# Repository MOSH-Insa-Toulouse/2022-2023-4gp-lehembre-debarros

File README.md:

# 2022-2023-4gp-lehembre-debarros

## SOMMAIRE 

1. Etapes de fabrication
2. Présentation du capteur graphite 
3. Simulations sous LtSpice
4. Circuit électronique
5. Eléments nécessaires au projet
6. Elaboration du shield sous KiCAD
7. Programme Arduino
8. Application Android
9. Banc de test
10. Datasheet 

# 1. Etapes de fabrication

- Création du circuit et simulations sous LtSpice
- Implémentation du circuit sous KiCAD et élaboration du PCB 
- Fabrication du PCB
- Percage de la plaquette et soudure des composants 
- Elaboration du code Arduino
- Création de l'application d'interfacage sous MIT - app inventor
- Caractérisation du capteur

# 2. Présentation du capteur graphite 

Le capteur est basé sur l'effet tunnel quantique entre les particules de graphite déposées par le crayon. 
Pour plus d'informations, vous pouvez vous renseigner grâce au lien suivant : [Informations supplémentaires](https://github.com/MOSH-Insa-Toulouse/2022-2023-4gp-lehembre-debarros/blob/d776b440ef20fb4f5e64abb67d3f56df1f3a449e/++Publi%20Pencil%20Drawn%20Strain%20Gauges-srep03812.pdf)

Dimensions : 

Utilisation d'un crayon HB pour le grain.

# 3. Simulations sous LtSpice

Etude et dimensionnement du gain et des capacités afin d’obtenir un signal exploitable en simulant le circuit : 

La résistance du capteur est calculé grâce à la formule suivante : 𝑅_𝐶=((𝑅_3+𝑅_2) 𝑅_1 𝑉_𝐶𝐶)/(𝑅_2 𝑉_𝐴𝐷𝐶)−𝑅_5−𝑅_1

# 4. Circuit électronique 

Schéma de l'amplificateur de signal :

Modules supplémentaires et leur connexions : 

Connection des pins entre le PCB et la carte Arduino

# 5. Eléments nécessaires au projet 

-	Arduino Uno
-	Module Bluetooth HC05
-	Amplificateur LTC1050 
-	I2C Ecran OLED Joy-it SBC-OLED01
-	Encodeur rotatoire avec boutton poussoir (Joy-it KY-040) 
-	Spectrasymbol 005 21 Flex Sensor
-	MCP41050 SPI Potentiomètre Digital 

# 6. Elaboration du PCB sous KiCAD

Représentation du PCB avec le circuit implémenté : 

Empruntes des autres composants : 

# 7. Programme Arduino

Ci-après, le code Arduino utilisé : [Code Arduino](https://github.com/MOSH-Insa-Toulouse/2022-2023-4gp-lehembre-debarros/blob/07b504035136efd2108f1f7b01446d1b1bee7c57/Code_arduino_Lauriane_Alan.ino)

# 8. Application Android

L'APK est disponible à cette adresse : [APK](https://github.com/MOSH-Insa-Toulouse/2022-2023-4gp-lehembre-debarros/blob/c0ea48ad6c8dff68e6e4c520c7baa0256ce2a0f2/Capteur_Graphite_Final.apk)

# 9. Banc de test

Pour calibrer notre capteur, nous avons utilisé le banc de test mis à notre disposition. 

Nous avons ainsi obtenu les variations relatives suivantes en tension et en compression : 

Notre capteur dispose ainsi d'une sensibilité de 0,675 GΩ/% en compression et 0,2GΩ/% en tension.

Cette sensibilité correspond au coefficient de la pente de la variation relative par rapport à la déformation. 
La déformation se calcule à l'aide de la formule suivante : ɛ = e/(2.R).

- ɛ : déformation
- e : épaisseur du papier utilisé (0,16mm ici)
- R : rayon de la courbe

These values are for comparative use only to get orders of magnitude, they are very unstable until the sensor is stabilized in a specialized housing. 

# 10. Datasheet

La datasheet est disponible en suivante le lien ci-après : [Datasheet](https://github.com/MOSH-Insa-Toulouse/2022-2023-4gp-lehembre-debarros/blob/0e1e4ce1e155748c3f02e4ec9dddf21011c97965/Datasheet%20-%20Capteur-final.pdf)

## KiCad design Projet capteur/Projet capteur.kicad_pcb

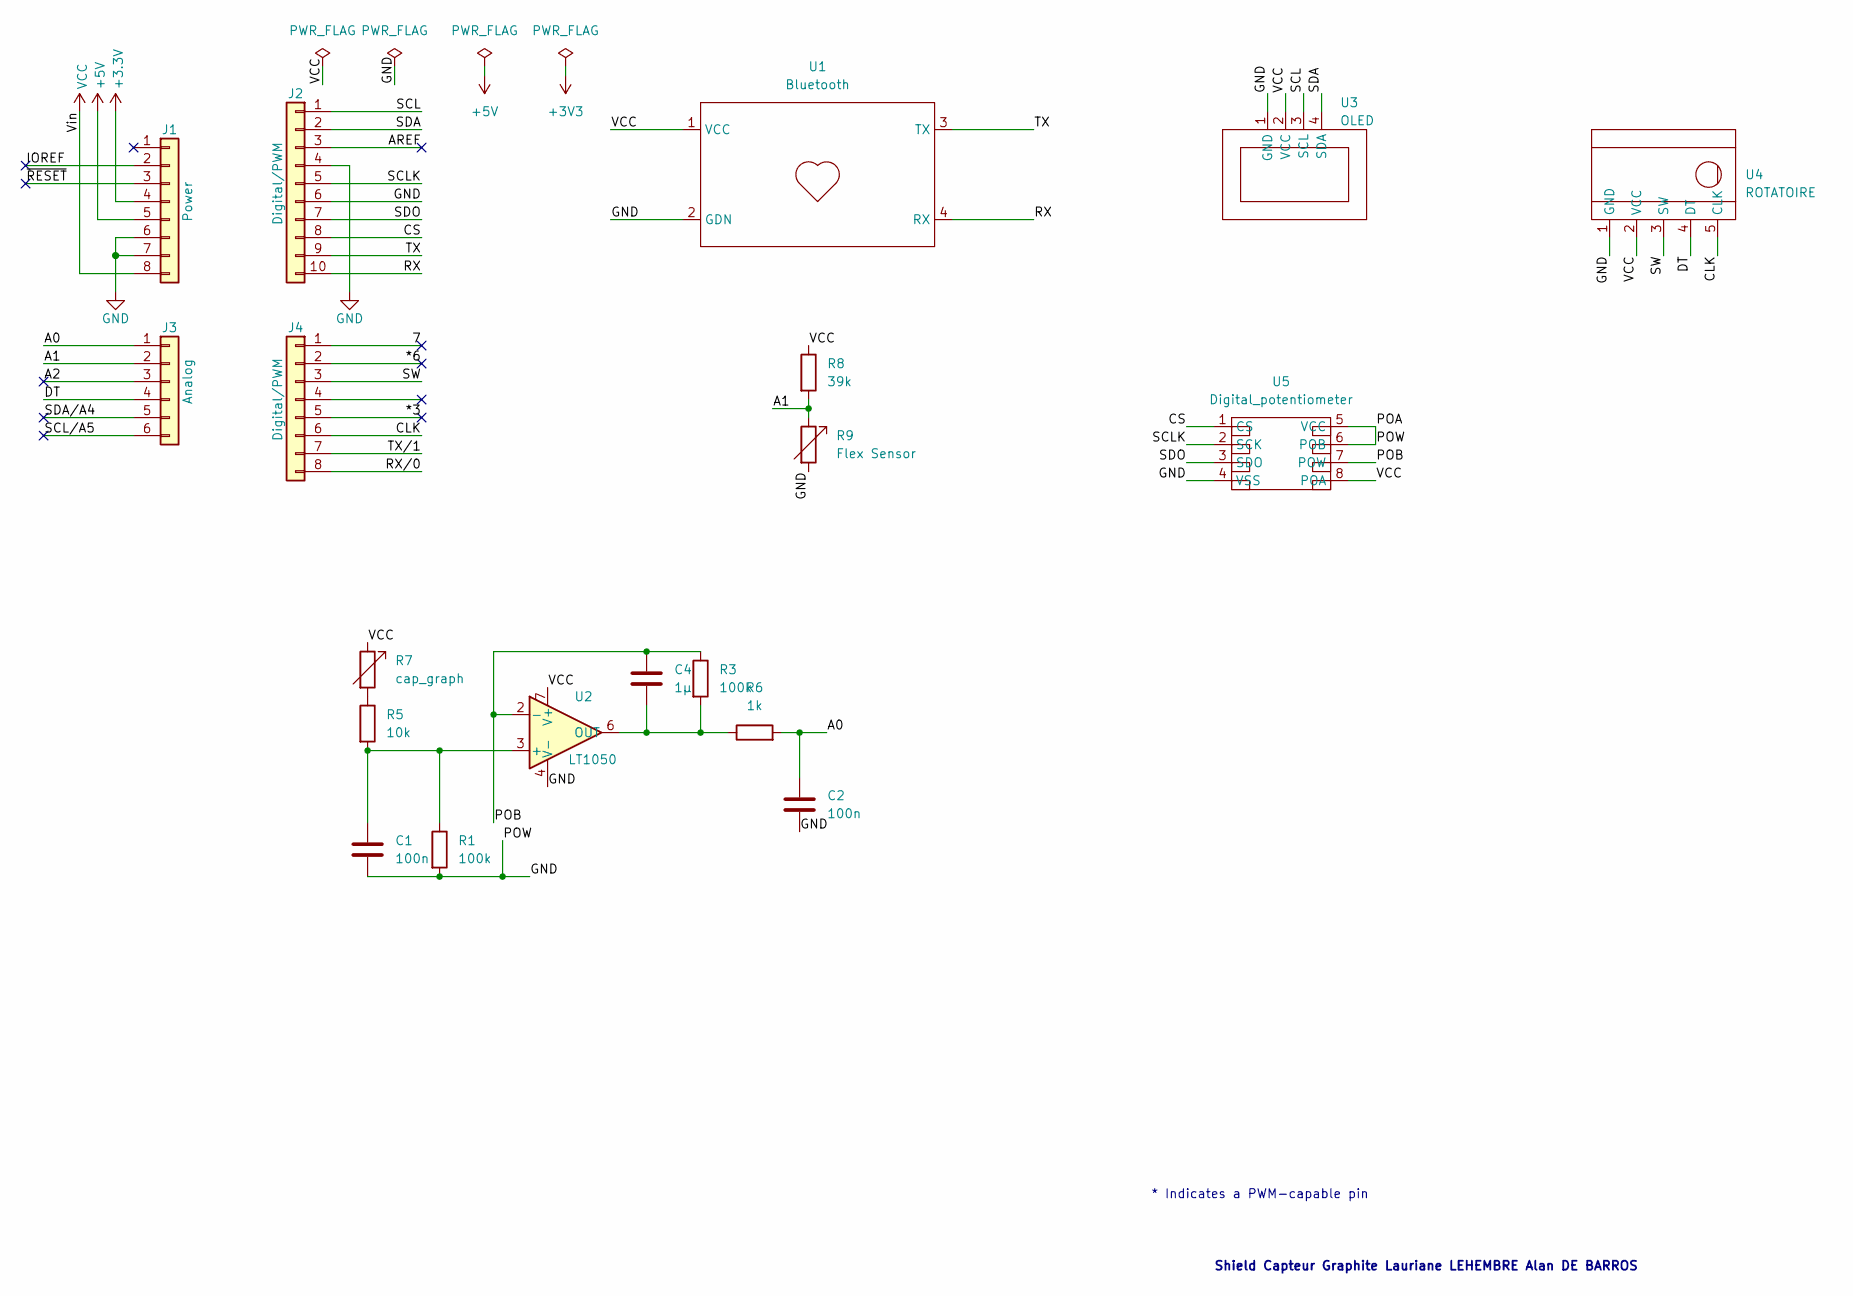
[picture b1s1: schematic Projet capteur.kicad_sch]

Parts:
C1, C2: 100n; capa
C4: 1µ; C4
J1: Power; PinSocket_1x08_P2.54mm_Vertical
J2: Digital/PWM; PinSocket_1x10_P2.54mm_Vertical
J3: Analog; PinSocket_1x06_P2.54mm_Vertical
J4: Digital/PWM; PinSocket_1x08_P2.54mm_Vertical
R1, R3: 100k; Resistance
R5: 10k; Resistance
R6: 1k; Resistance
R7: cap_graph; Flex_sensor
R8: 39k; Resistance
R9: Flex Sensor; Flex_sensor
U1: Bluetooth; Bluetooth_4pattes
U2: LT1050; DIP-8_W7.62mm_LongPads
U3: OLED
U4: ROTATOIRE; Rotatoire
U5: Digital_potentiometer; Pot_Digital

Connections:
+3V3: J1.4
+5V: J1.5
/7: J4.1
/*3: J4.5
/*6: J4.2
/A0: C2.1, J3.1, R6.2
/A1: J3.2, R8.2, R9.1
/A2: J3.3
/AREF: J2.3
/CLK: J4.6, U4.5 (CLK)
/CS: J2.8, U5.1 (CS)
/DT: J3.4, U4.4 (DT)
/IOREF: J1.2
/POB: C4.1, R3.1, U2.2 (-), U5.7 (POW)
/RX: J2.10, U1.4 (RX)
/RX/0: J4.8
/SCL: J2.1, U3.3 (SCL)
/SCLK: J2.5, U5.2 (SCK)
/SCL/A5: J3.6
/SDA: J2.2, U3.4 (SDA)
/SDA/A4: J3.5
/SDO: J2.7, U5.3 (SDO)
/SW: J4.3, U4.3 (SW)
/TX: J2.9, U1.3 (TX)
/TX/1: J4.7
/~RESET: J1.3
GND: C1.2, C2.2, J1.6, J1.7, J2.4, J2.6, R1.2, R9.2, U1.2 (GDN), U2.4 (V-), U3.1 (GND), U4.1 (GND), U5.4 (VSS), U5.5 (VCC), U5.6 (POB)
unnamed: R5.1, R7.2
unnamed: C1.1, R1.1, R5.2, U2.3 (+)
unnamed: C4.2, R3.2, R6.1, U2.6 (OUT)
VCC: J1.8, R7.1, R8.1, U1.1 (VCC), U2.7 (V+), U3.2 (VCC), U4.2 (VCC), U5.8 (POA)

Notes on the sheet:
Shield Capteur Graphite Lauriane LEHEMBRE Alan DE BARROS
* Indicates a PWM-capable pin

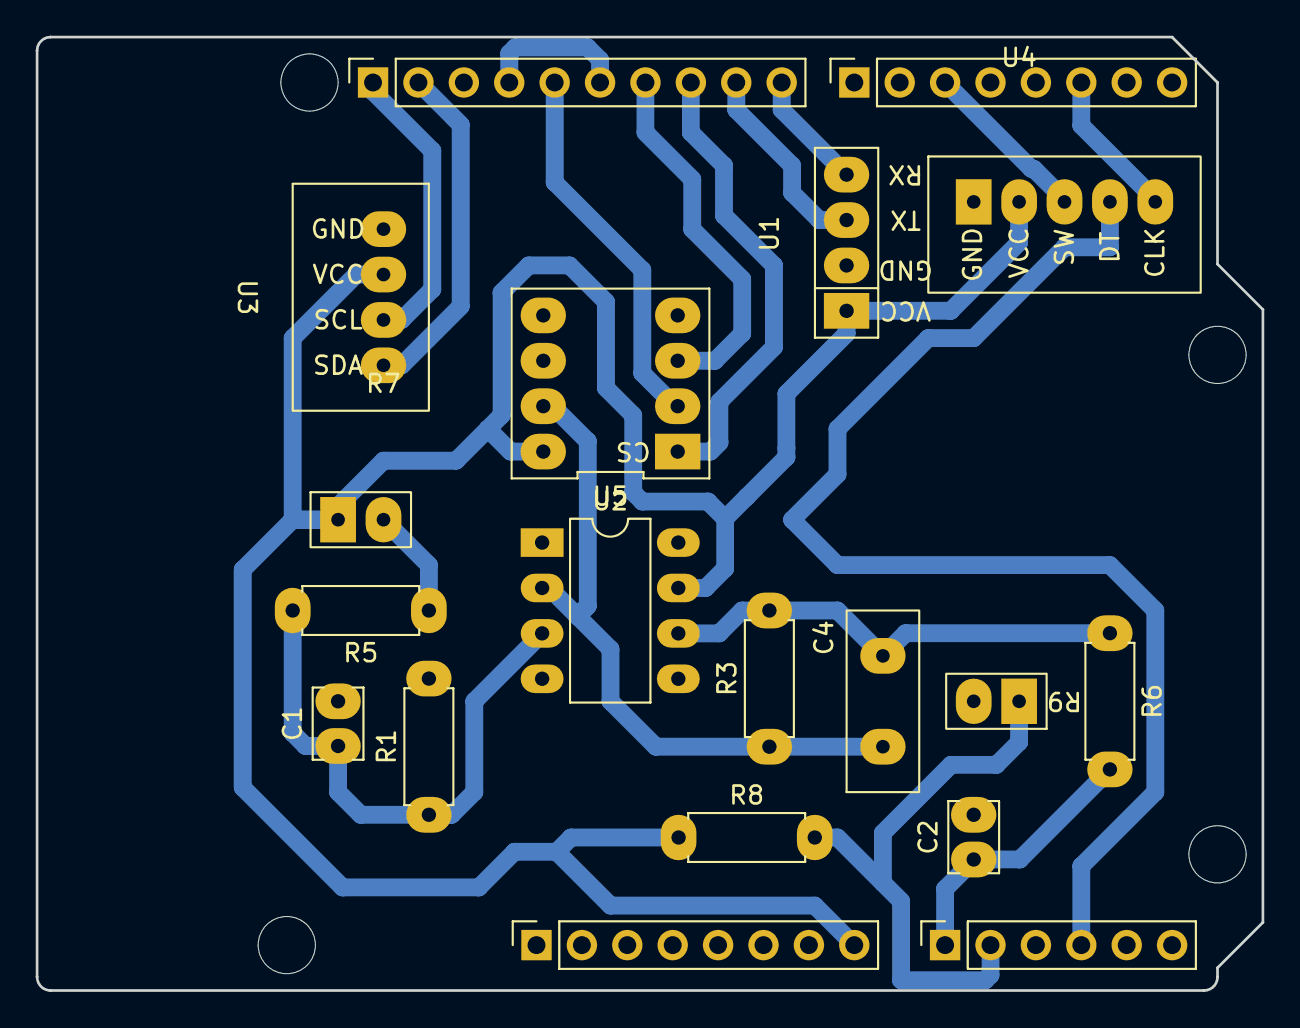
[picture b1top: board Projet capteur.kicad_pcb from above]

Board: 2 copper layers, 68.6 x 53.3 mm, 23 parts (0 on the bottom side), 18 nets.

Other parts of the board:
MH1, MH2, MH3, MH4: MountingHole_3.2mm

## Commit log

2023-02-03 Changement Alan
2023-02-03 changement lauriane 2
2023-02-03 Changement Alan v2
2023-02-03 changement Lauriane 1
2023-02-03 azertyuio
2023-02-03 Changement v3 alan
2023-02-03 kjdizoj
2023-02-03 azertyujikol
2023-02-03 Test resov merge
2023-04-21 Create Datasheet
2023-04-21 Update Datasheet
2023-04-21 Ajout du code arduino
2023-04-21 APK de l'application Android
2023-05-11 Ajout fichiers ltspice
